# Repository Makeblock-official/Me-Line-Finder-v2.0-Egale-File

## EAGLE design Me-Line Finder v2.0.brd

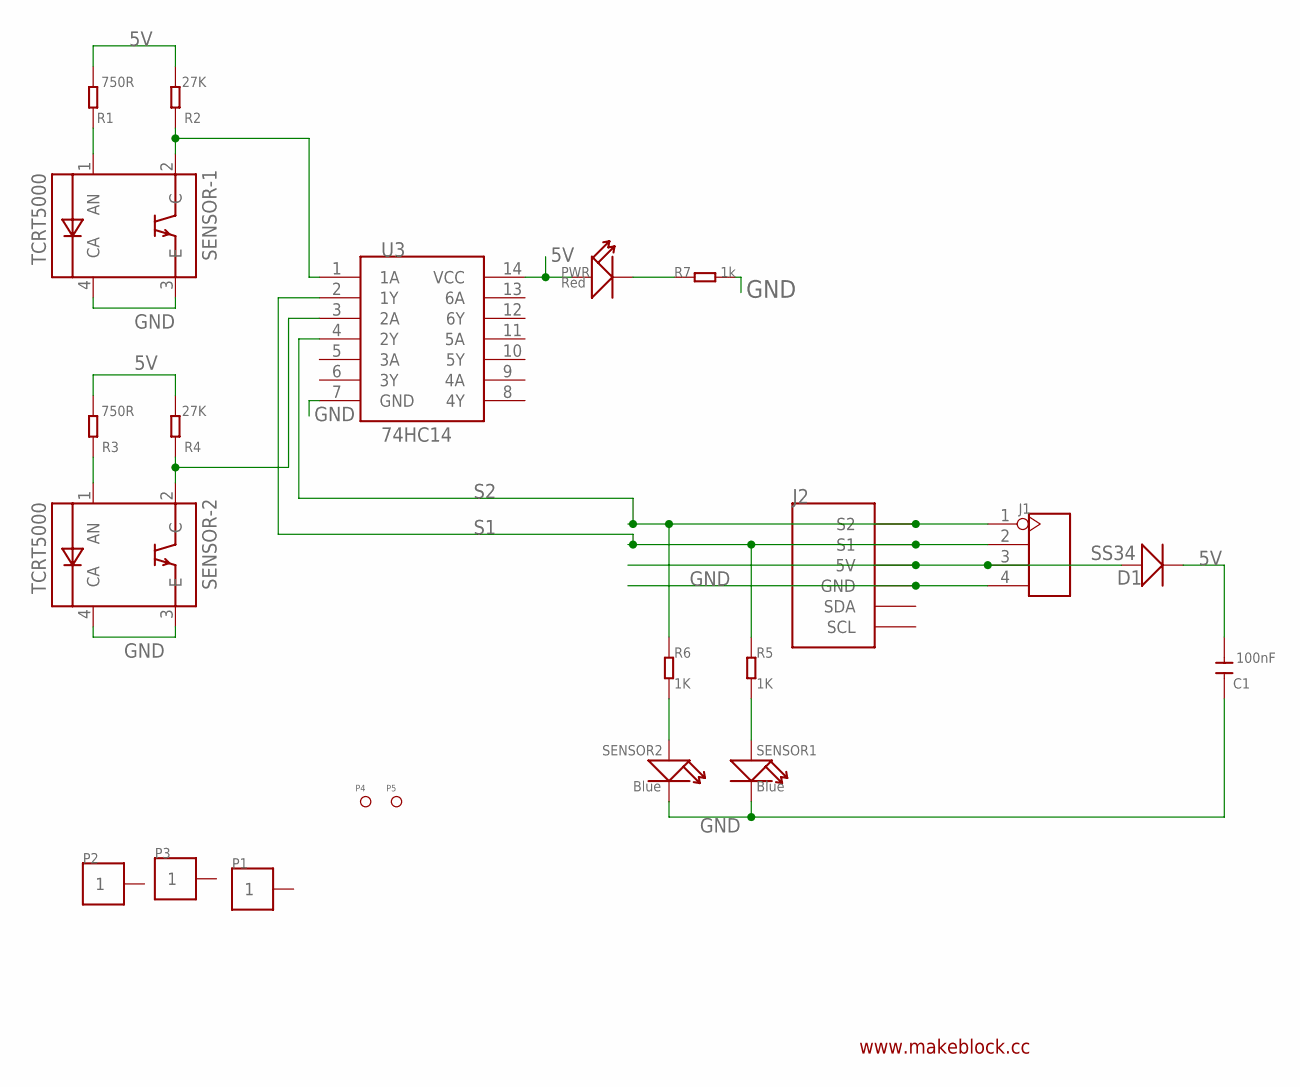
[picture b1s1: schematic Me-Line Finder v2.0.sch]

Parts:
C1: 100nF; 0603
D1: SS34; D2010
J1: HEADER-4P-60/35MIL; 4P-65/35MIL
J2: RJ11-6P6C-DIGI; RJ11-6P6C
P1, P2, P3: PAD-1P-4MM; HOLE-01
P4, P5: PAD-MARK; ROUND-MARK-1.0
PWR: Red; LED-0603
R1, R3: 750R; 0603
R2, R4: 27K; 0603
R5, R6: 1K; 0603
R7: 1k; 0603
SENSOR1, SENSOR2: Blue; LED-0603
SENSOR-1, SENSOR-2: TCRT5000
U3: 74HC14; TSSOP14

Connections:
5V: C1.2, D1.-, PWR.+, R1.2, R2.2, R3.2, R4.2, U3.14 (VCC)
GND: C1.1, J1.4, J2.3 (GND), R7.2, SENSOR1.-, SENSOR2.-, SENSOR-1.3 (E), SENSOR-1.4 (CA), SENSOR-2.3 (E), SENSOR-2.4 (CA), U3.7 (GND)
unnamed: R5.2, SENSOR1.+
unnamed: R6.2, SENSOR2.+
unnamed: R2.1, SENSOR-1.2 (C), U3.1 (1A)
unnamed: R1.1, SENSOR-1.1 (AN)
unnamed: R4.1, SENSOR-2.2 (C), U3.3 (2A)
unnamed: R3.1, SENSOR-2.1 (AN)
unnamed: PWR.-, R7.1
unnamed: D1.+, J1.3, J2.4 (5V)
S1: J1.2, J2.5 (S1), R5.1, U3.2 (1Y)
S2: J1.1, J2.6 (S2), R6.1, U3.4 (2Y)

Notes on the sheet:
www.makeblock.cc

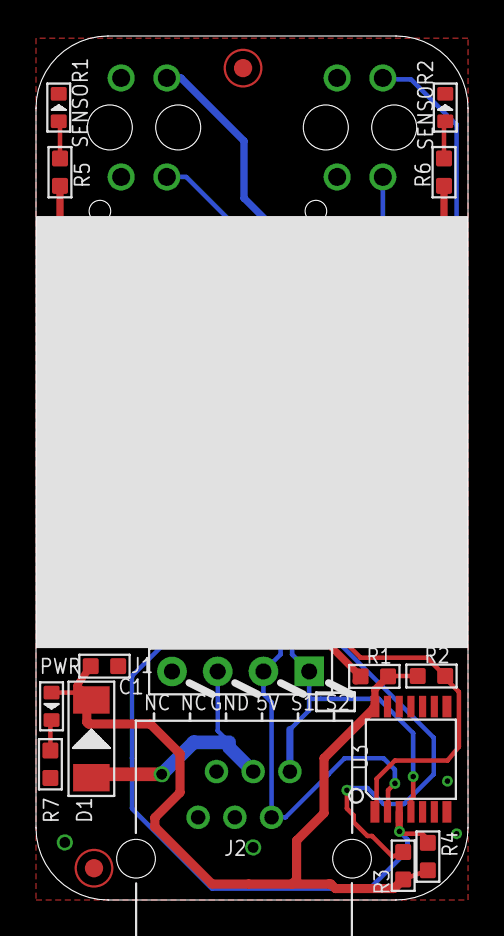
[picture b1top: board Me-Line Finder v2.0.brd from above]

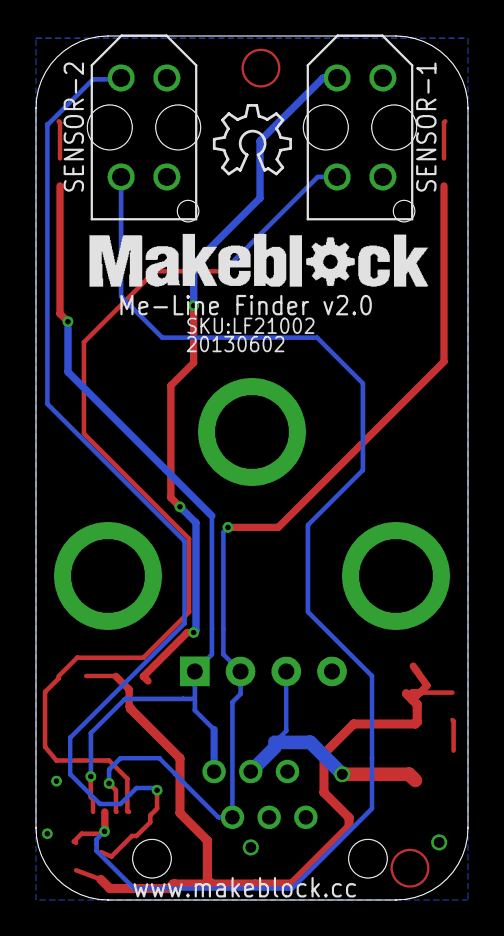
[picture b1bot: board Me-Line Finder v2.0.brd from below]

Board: 2 copper layers, 24.0 x 48.0 mm, 24 parts (7 on the bottom side), 12 nets.

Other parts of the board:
U$1: LOGO-3/2
U$2: OSHW_6X150_NOTEXT

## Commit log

2013-08-27 PCB files
